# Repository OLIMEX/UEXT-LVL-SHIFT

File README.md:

# UEXT-LVL-SHIFT
UEXT level shift module allow boards with UEXT connector to interface modules with voltage levels from 1.65V to 5.5V

https://www.olimex.com/Products/Modules/Adapters/UEXT-LVL-SHIFT/open-source-hardware

## Licensee
* Hardware is released under CERN Open Hardware Licence Version 2 - Strongly Reciprocal, all silkscreen credits to Bernardo Kastrup and Dean Belfield should remain;
* Software is released under MIT Licensee
* Documentation is released under CC BY-SA 3.0

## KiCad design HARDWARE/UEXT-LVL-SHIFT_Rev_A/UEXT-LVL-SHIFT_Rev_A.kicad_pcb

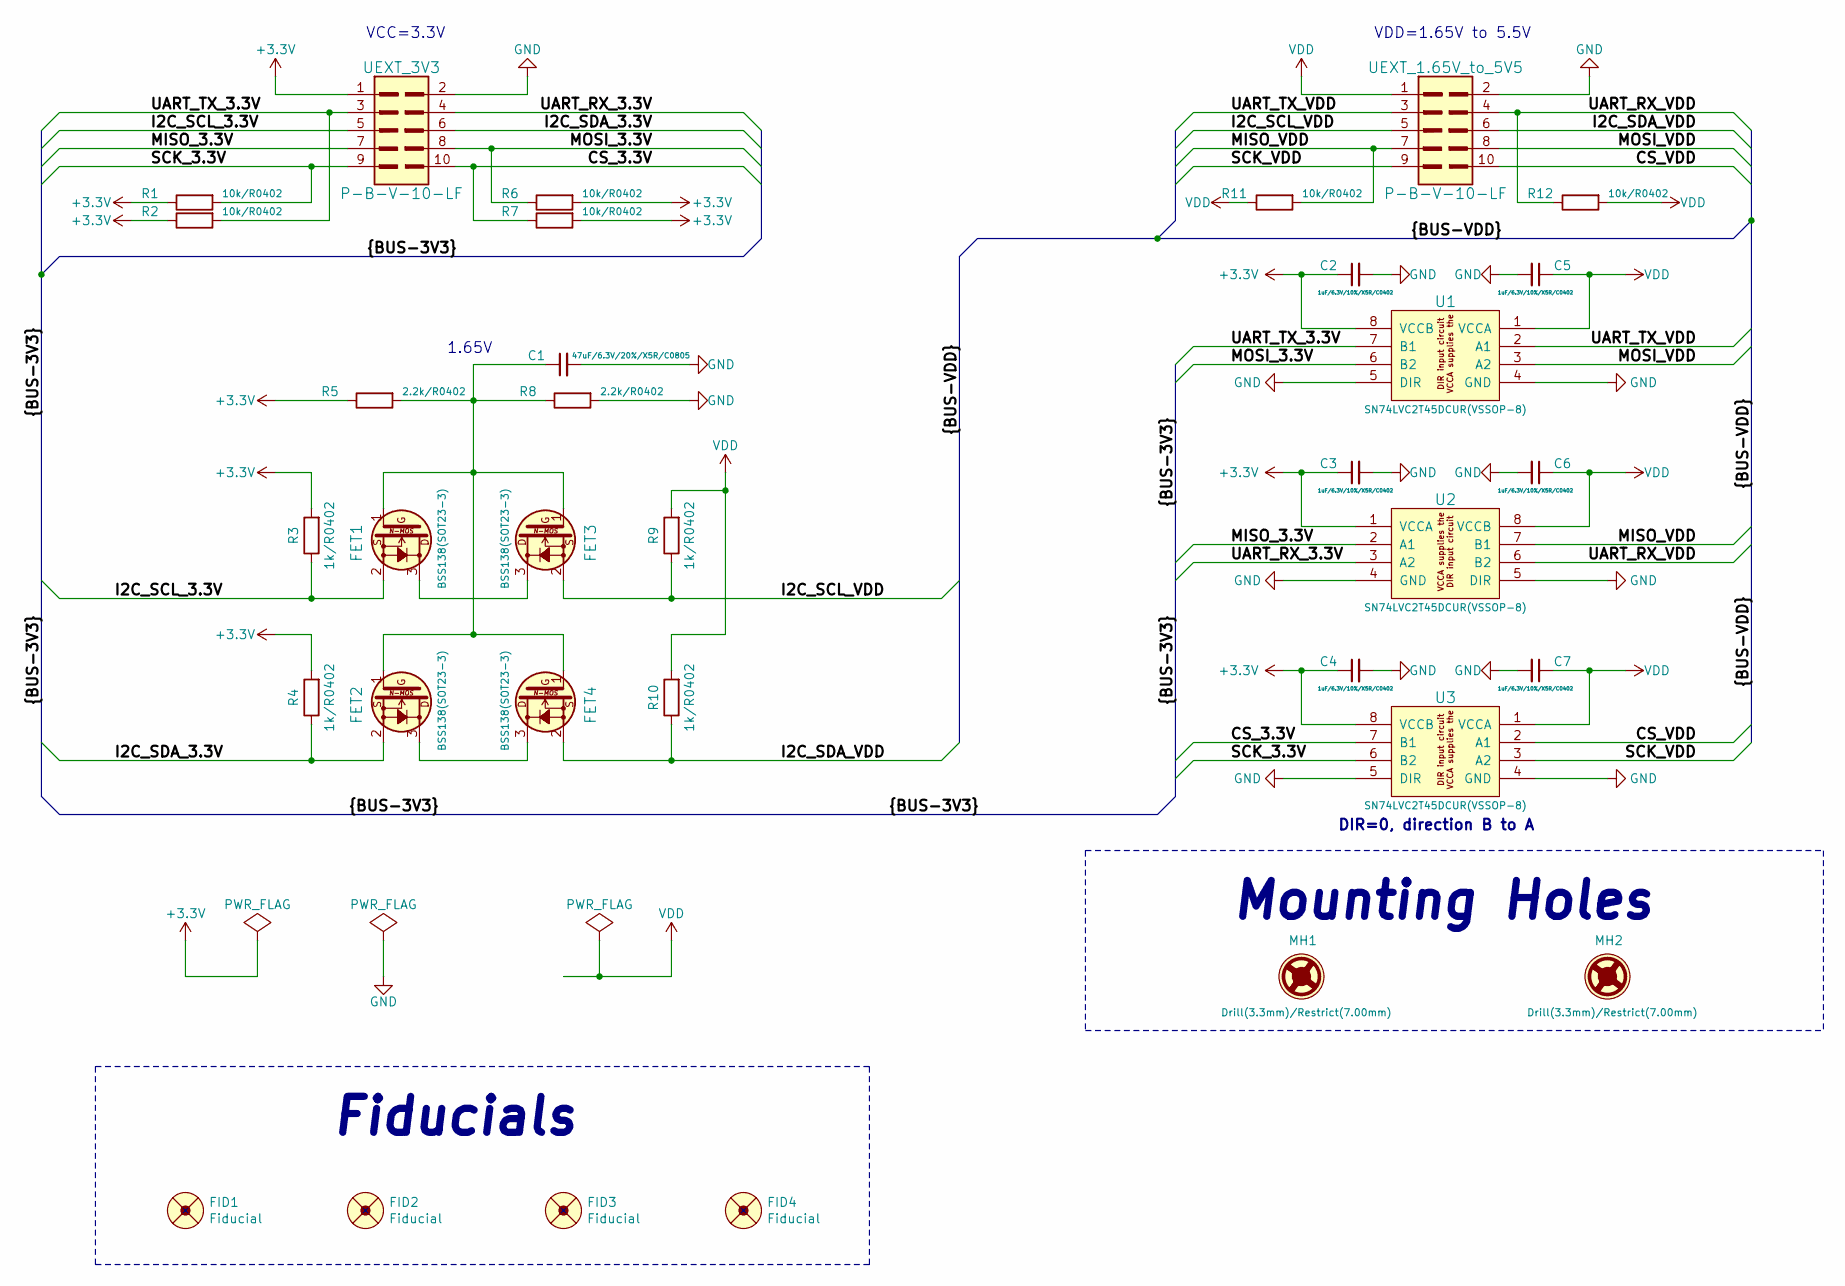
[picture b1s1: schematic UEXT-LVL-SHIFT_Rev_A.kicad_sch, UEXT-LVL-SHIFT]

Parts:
C1: 47uF/6.3V/20%/X5R/C0805; C_0805_5MIL_DWS
C2, C3, C4, C5, C6, C7: 1uF/6.3V/10%/X5R/C0402; C_0402_5MIL_DWS
FET1, FET2, FET3, FET4: BSS138(SOT23-3); SOT23
FID1, FID3: Fiducial; Fiducial1x3
FID2, FID4: Fiducial; Fiducial1x3_Paste
MH1, MH2: Drill(3.3mm)/Restrict(7.00mm); Mounting_Hole_Drill-3.3mm_Clerance-7mm
R1, R2, R6, R7, R11, R12: 10k/R0402; R_0402_5MIL_DWS
R3, R4, R9, R10: 1k/R0402; R_0402_5MIL_DWS
R5, R8: 2.2k/R0402; R_0402_5MIL_DWS
U1, U2, U3: SN74LVC2T45DCUR(VSSOP-8); VSSOP-8_Pitch-0.50mm_Pad-0.25mm_Dimensions-2.30x2.00x1.00mm
UEXT_1.65V_to_5V5, UEXT_3V3: P-B-V-10-LF; GBH-254-SMT-10

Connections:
+3.3V: C2.1, C3.1, C4.1, R1.1, R2.1, R3.2, R4.2, R5.1, R6.2, R7.2, U1.8 (VCCB), U2.1 (VCCA), U3.8 (VCCB), UEXT_3V3.1
/CS_3.3V: R7.1, U3.7 (B1), UEXT_3V3.10
/CS_VDD: U3.2 (A1), UEXT_1.65V_to_5V5.10
/I2C_SCL_3.3V: FET1.2 (S), R3.1, UEXT_3V3.5
/I2C_SCL_VDD: FET3.2 (S), R9.1, UEXT_1.65V_to_5V5.5
/I2C_SDA_3.3V: FET2.2 (S), R4.1, UEXT_3V3.6
/I2C_SDA_VDD: FET4.2 (S), R10.1, UEXT_1.65V_to_5V5.6
/MISO_3.3V: U2.2 (A1), UEXT_3V3.7
/MISO_VDD: R11.2, U2.7 (B1), UEXT_1.65V_to_5V5.7
/MOSI_3.3V: R6.1, U1.6 (B2), UEXT_3V3.8
/MOSI_VDD: U1.3 (A2), UEXT_1.65V_to_5V5.8
/SCK_3.3V: R1.2, U3.6 (B2), UEXT_3V3.9
/SCK_VDD: U3.3 (A2), UEXT_1.65V_to_5V5.9
/UART_RX_3.3V: U2.3 (A2), UEXT_3V3.4
/UART_RX_VDD: R12.1, U2.6 (B2), UEXT_1.65V_to_5V5.4
/UART_TX_3.3V: R2.2, U1.7 (B1), UEXT_3V3.3
/UART_TX_VDD: U1.2 (A1), UEXT_1.65V_to_5V5.3
GND: C1.2, C2.2, C3.2, C4.2, C5.2, C6.2, C7.2, R8.2, U1.4 (GND), U1.5 (DIR), U2.4 (GND), U2.5 (DIR), U3.4 (GND), U3.5 (DIR), UEXT_1.65V_to_5V5.2, UEXT_3V3.2
unnamed: FET1.3 (D), FET3.3 (D)
unnamed: C1.1, FET1.1 (G), FET2.1 (G), FET3.1 (G), FET4.1 (G), R5.2, R8.1
unnamed: FET2.3 (D), FET4.3 (D)
VDD: C5.1, C6.1, C7.1, R9.2, R10.2, R11.1, R12.2, U1.1 (VCCA), U2.8 (VCCB), U3.1 (VCCA), UEXT_1.65V_to_5V5.1

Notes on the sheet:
VDD=1.65V to 5.5V
DIR=0, direction B to A
Mounting Holes
1.65V
Fiducials
VCC=3.3V

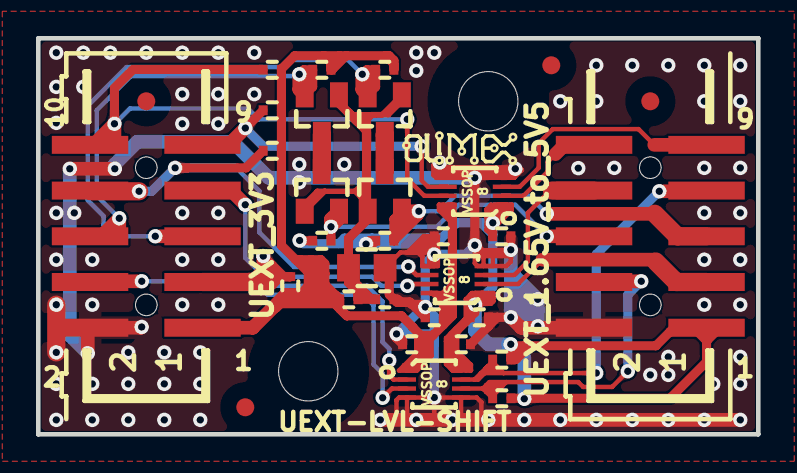
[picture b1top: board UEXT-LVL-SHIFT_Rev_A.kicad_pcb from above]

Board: 2 copper layers, 40.0 x 22.0 mm, 42 parts (7 on the bottom side), 22 nets.

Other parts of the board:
Logo_OLIMEX_SMALL_TB: Logo_OLIMEX_SMALL_TB
Logo_OLIMEX_TB-Top: Logo_OLIMEX_TB
Sign_Antistatic: Sign_Antistatic
Sign_CE: CE_Sign
Sign_OSHW_8x8: Sign_OSHW_8x8
Sign_PB-Free: Sign_PB-Free
Sign_RecycleBin: Sign_RecycleBin; Sign_RecycleBin_1
Sign_RoHS: Sign_RoHS; Sign_RoHS_1

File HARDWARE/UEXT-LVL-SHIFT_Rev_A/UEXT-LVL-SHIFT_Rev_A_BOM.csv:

Quantity,Value,Footprint,Reference
1,47uF/6.3V/20%/X5R/C0805,C_0805_5MIL_DWS,C1
6,1uF/6.3V/10%/X5R/C0402,C_0402_5MIL_DWS,"C2, C3, C4, C5, C6, C7"
4,BSS138(SOT23-3),SOT23,"FET1, FET2, FET3, FET4"
6,10k/R0402,R_0402_5MIL_DWS,"R1, R2, R6, R7, R11, R12"
4,1k/R0402,R_0402_5MIL_DWS,"R3, R4, R9, R10"
2,2.2k/R0402,R_0402_5MIL_DWS,"R5, R8"
3,SN74LVC2T45DCUR(VSSOP-8),VSSOP-8_Pitch-0.50mm_Pad-0.25mm_Dimensions-2.30x2.00x1.00mm,"U1, U2, U3"
2,P-B-V-10-LF,GBH-254-SMT-10,"UEXT_1.65V_to_5V5, UEXT_3V3"

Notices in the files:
HARDWARE/UEXT-LVL-SHIFT_Rev_A/UEXT-LVL-SHIFT_Rev_A.kicad_pcb:
(C) 2026
